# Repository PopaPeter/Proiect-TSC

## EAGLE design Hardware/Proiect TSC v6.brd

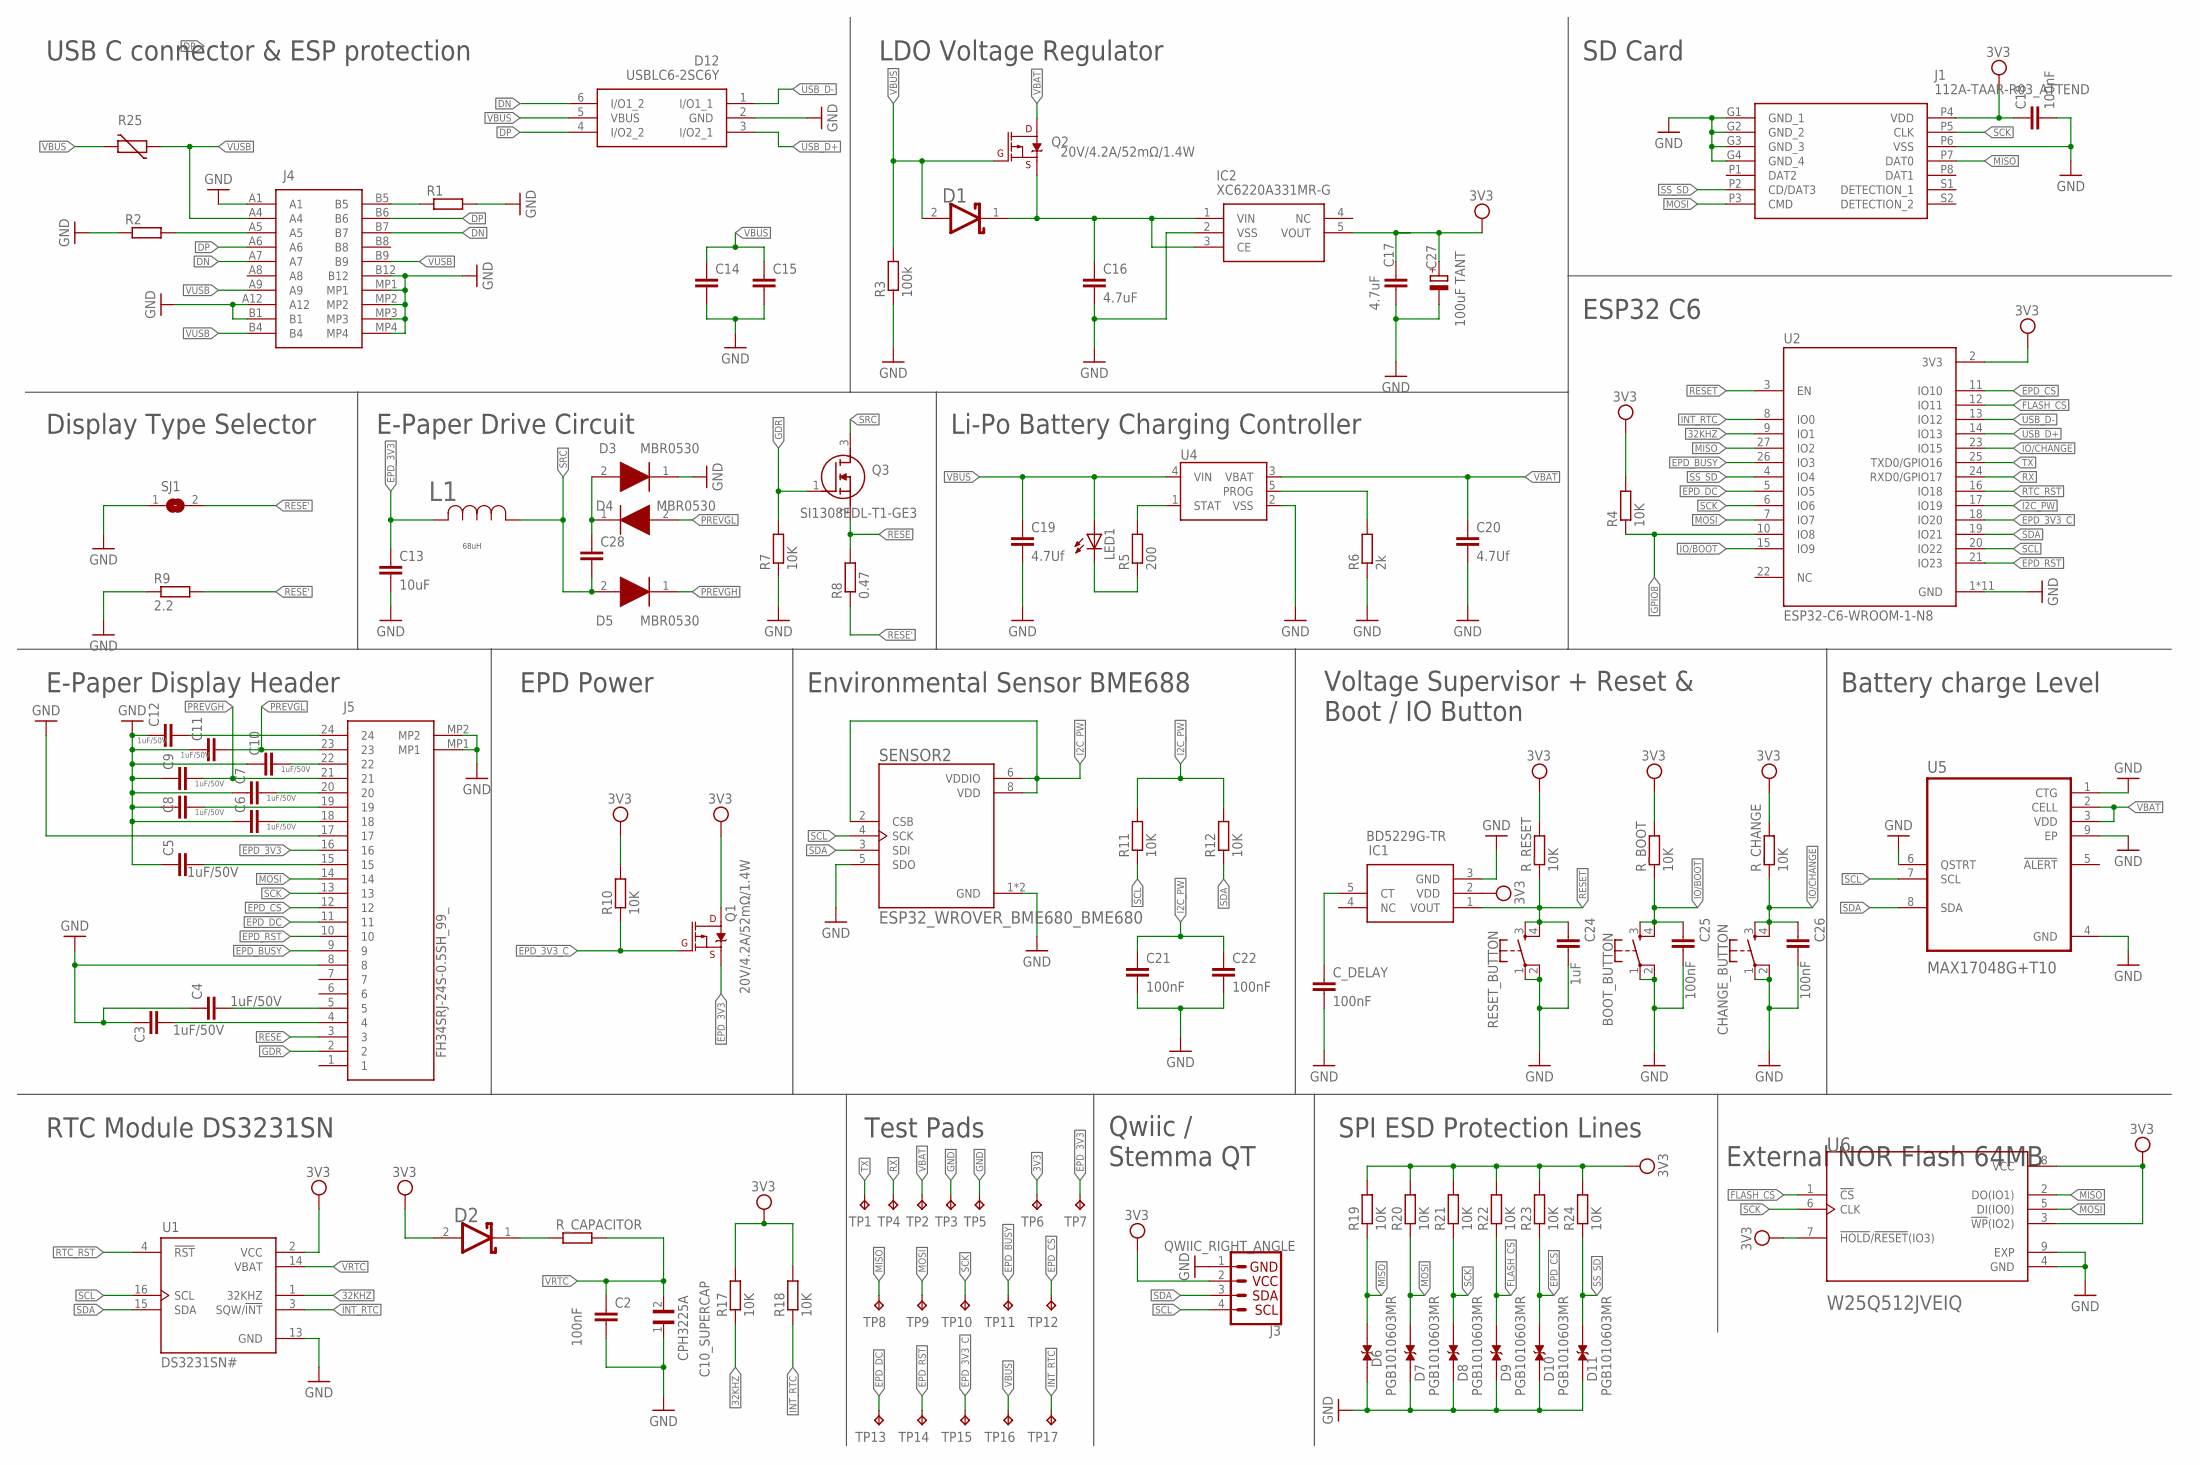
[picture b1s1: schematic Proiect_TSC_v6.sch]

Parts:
BOOT_BUTTON: BUTTON_CUSYOMV1; MYBUTTON
C2, C18, C21, C22, C25, C26: 100nF; ESP32_WROVER_EAGLE-LTSPICE_C0402
C3, C4, C5, C6, C7, C8, C9, C10, C11, C12: 1uF/50V; ESP32_WROVER_EAGLE-LTSPICE_C0402
C10_SUPERCAP: CPH3225A; CAPCP3225X100N
C13: 10uF; ESP32_WROVER_EAGLE-LTSPICE_C0402
C14, C15, C28: ESP32_WROVER_EAGLE-LTSPICE_CC0402; ESP32_WROVER_EAGLE-LTSPICE_C0402
C16, C17: 4.7uF; ESP32_WROVER_EAGLE-LTSPICE_C0402
C19, C20: 4.7Uf; ESP32_WROVER_EAGLE-LTSPICE_C0402
C24: 1uF; ESP32_WROVER_EAGLE-LTSPICE_C0402
C27: 100uF TANT; RCL_CT3528
CHANGE_BUTTON: BUTTON_CUSYOMV1; MYBUTTON
C_DELAY: 100nF; ESP32_WROVER_EAGLE-LTSPICE_C0402
D1, D2: ESP32_WROVER_AVX---SD0805S020S1R0_AVX_SD0805S020S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; ESP32_WROVER_AVX---SD0805S020S1R0_AVX_SD0805S020S1R0_0
D3, D4, D5: MBR0530; SOD3716X135N
D6, D7, D8, D9, D10, D11: PGB1010603MR; DIOC1608X36N
D12: USBLC6-2SC6Y; SOT95P280X145-6N
IC1: BD5229G-TR; SOT95P280X125-5N
IC2: XC6220A331MR-G; SOT95P280X120-5N
J1: 112A-TAAR-R03_ATTEND; 112ATAARR03ATTEND
J3: QWIIC_RIGHT_ANGLE; JST04_1MM_RA
J4: SAMACSYS_PARTS_USB4110-GF-A; SAMACSYS_PARTS_USB4110GFA
J5: FH34SRJ-24S-0.5SH_99_; FH34SRJ24S05SH99
L1: 744043680IND_4828-WE-TPC_WRE; IND_4828-WE-TPC_WRE
LED1: ADAFRUIT_LEDCHIP-LED0603; ADAFRUIT_CHIP-LED0603
Q1, Q2: 20V/4.2A/52mΩ/1.4W; ESP32_WROVER_SPARKFUN-DISCRETESEMI_SOT23-3
Q3: SI1308EDL-T1-GE3; SOT65P210X110-3N
R1, R2: ESP32_WROVER_EAGLE-LTSPICE_RR0402; ESP32_WROVER_EAGLE-LTSPICE_R0402
R3: 100k; ESP32_WROVER_EAGLE-LTSPICE_R0402
R4, R7, R10, R11, R12, R17, R18, R19, R20, R21, R22, R23, R24: 10K; ESP32_WROVER_EAGLE-LTSPICE_R0402
R5: 200; ESP32_WROVER_EAGLE-LTSPICE_R0402
R6: 2k; ESP32_WROVER_EAGLE-LTSPICE_R0402
R8: 0.47; ESP32_WROVER_EAGLE-LTSPICE_R0402
R9: 2.2; ESP32_WROVER_EAGLE-LTSPICE_R0402
R25: ESP32C6_VARISTORCN1812; ESP32C6_VARISTOR_CT/CN1812
RESET_BUTTON: BUTTON_CUSYOMV1; MYBUTTON
R_BOOT: 10K; ESP32_WROVER_EAGLE-LTSPICE_R0402
R_CAPACITOR: ESP32_WROVER_EAGLE-LTSPICE_RR0402; ESP32_WROVER_EAGLE-LTSPICE_R0402
R_CHANGE: 10K; ESP32_WROVER_EAGLE-LTSPICE_R0402
R_RESET: 10K; ESP32_WROVER_EAGLE-LTSPICE_R0402
SENSOR2: ESP32_WROVER_BME680_BME680; ESP32_WROVER_BME680_PSON80P300X300X100-8N
SJ1: SJ
TP1, TP2, TP3, TP4, TP5, TP6, TP7, TP8, TP9, TP10, TP11, TP12, TP13, TP14, TP15, TP16, TP17: TPTP20R; TP20R
U1: DS3231SN#; SOIC127P1032X265-16N
U2: ESP32-C6-WROOM-1-N8; XCVR_ESP32-C6-WROOM-1-N8
U4: ESP32_WROVER_SPARKFUN-IC-POWER_MCP73831; ESP32_WROVER_SPARKFUN-IC-POWER_SOT23-5
U5: MAX17048G+T10; SON50P200X200X80-9N
U6: W25Q512JVEIQ; SON127P600X800X80-9N

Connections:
3V3: C18.1, D2.2 (ANODE), IC1.2 (VDD), J1.P4 (VDD), J3.2, Q1.3 (D), R4.2, R10.2, R17.2, R18.2, R19.2, R20.2, R21.2, R22.2, R23.2, R24.2, R_BOOT.2, R_CHANGE.2, R_RESET.2, TP6.TP, U1.2 (VCC), U2.2 (3V3), U6.3 (!WP!(IO2)), U6.7 (!HOLD!/!RESET!(IO3)), U6.8 (VCC)
32KHZ: R17.1, U1.1 (32KHZ), U2.9 (IO1)
DN: D12.6 (I/O1_2), J4.A7, J4.B7
DP: D12.4 (I/O2_2), J4.A6, J4.B6
EPD_3V3: C13.1, J5.16, L1.2, Q1.2 (S), TP7.TP
EPD_3V3_C: Q1.1 (G), R10.1, TP15.TP, U2.18 (IO20)
EPD_BUSY: J5.9, TP11.TP, U2.26 (IO3)
EPD_CS: D10.2, J5.12, R23.1, TP12.TP, U2.11 (IO10)
EPD_DC: J5.11, TP13.TP, U2.5 (IO5)
EPD_RST: J5.10, TP14.TP, U2.21 (IO23)
FLASH_CS: D9.2, R22.1, U2.12 (IO11), U6.1 (!CS)
GDR: J5.2, Q3.1 (G), R7.2
GND: BOOT_BUTTON.1, BOOT_BUTTON.2, C2.2, C3.1, C4.1, C5.1, C6.1, C7.1, C8.1, C9.1, C10.1, C10_SUPERCAP.1, C11.1, C12.1, C13.2, C14.2, C15.2, C16.2, C17.2, C18.2, C19.2, C20.2, C21.2, C22.2, C24.2, C25.2, C26.2, C27.-, CHANGE_BUTTON.1, CHANGE_BUTTON.2, C_DELAY.2, D4.1 (K), D6.1, D7.1, D8.1, D9.1, D10.1, D11.1, D12.2 (GND), IC1.3 (GND), IC2.2 (VSS), J1.G1 (GND_1), J1.G2 (GND_2), J1.G3 (GND_3), J1.G4 (GND_4), J1.P6 (VSS), J3.1, J4.A1, J4.A12, J4.B1, J4.B12, J4.MP1, J4.MP2, J4.MP3, J4.MP4, J5.8, J5.17, J5.MP1, J5.MP2, R1.2, R2.1, R3.1, R6.1, R7.1, R9.1, RESET_BUTTON.1, RESET_BUTTON.2, SENSOR2.1 (GND), SENSOR2.5 (SDO), SENSOR2.7 (GND), SJ1.1, TP3.TP, TP5.TP, U1.13 (GND), U2.1 (GND), U2.28 (GND), U2.29_1 (GND), U2.29_2 (GND), U2.29_3 (GND), U2.29_4 (GND), U2.29_5 (GND), U2.29_6 (GND), U2.29_7 (GND), U2.29_8 (GND), U2.29_9 (GND), U4.2 (VSS), U5.1 (CTG), U5.4 (GND), U5.6 (QSTRT), U5.9 (EP), U6.4 (GND), U6.9 (EXP)
GPIO8: R4.1, U2.10 (IO8)
I2C_PW: C21.1, C22.1, R11.2, R12.2, SENSOR2.2 (CSB), SENSOR2.6 (VDDIO), SENSOR2.8 (VDD), U2.17 (IO19)
INT_RTC: R18.1, TP17.TP, U1.3 (SQW/!INT), U2.8 (IO0)
IO/BOOT: BOOT_BUTTON.3, BOOT_BUTTON.4, C25.1, R_BOOT.1, U2.15 (IO9)
IO/CHANGE: C26.1, CHANGE_BUTTON.3, CHANGE_BUTTON.4, R_CHANGE.1, U2.23 (IO15)
MISO: D6.2, J1.P7 (DAT0), R19.1, TP8.TP, U2.27 (IO2), U6.2 (DO(IO1))
MOSI: D7.2, J1.P3 (CMD), J5.14, R20.1, TP9.TP, U2.7 (IO7), U6.5 (DI(IO0))
unnamed: J4.A5, R2.2
unnamed: J4.B5, R1.1
unnamed: C16.1, D1.1 (CATHODE), IC2.1 (VIN), IC2.3 (CE), Q2.2 (S)
unnamed: C17.1, C27.+, IC2.5 (VOUT)
unnamed: R5.2, U4.1 (STAT)
unnamed: LED1.C, R5.1
unnamed: R6.2, U4.5 (PROG)
unnamed: C28.1, D3.1 (K), D4.2 (A)
unnamed: C12.2, J5.24
unnamed: C10.2, J5.22
unnamed: C7.2, J5.20
unnamed: C8.2, J5.19
unnamed: C6.2, J5.18
unnamed: C5.2, J5.15
unnamed: C4.2, J5.5
unnamed: C3.2, J5.4
unnamed: C_DELAY.1, IC1.5 (CT)
unnamed: U5.2 (CELL), U5.3 (VDD)
unnamed: D2.1 (CATHODE), R_CAPACITOR.1
PREVGH: C9.2, D5.1 (K), J5.21
PREVGL: C11.2, D3.2 (A), J5.23
RESE: J5.3, Q3.2 (S), R8.2
RESE': R8.1, R9.2, SJ1.2
RESET: C24.1, IC1.1 (VOUT), RESET_BUTTON.3, RESET_BUTTON.4, R_RESET.1, U2.3 (EN)
RTC_RST: U1.4 (!RST), U2.16 (IO18)
RX: TP4.TP, U2.24 (RXD0/GPIO17)
SCK: D8.2, J1.P5 (CLK), J5.13, R21.1, TP10.TP, U2.6 (IO6), U6.6 (CLK)
SCL: J3.4, R11.1, SENSOR2.4 (SCK), U1.16 (SCL), U2.20 (IO22)
SDA: J3.3, R12.1, SENSOR2.3 (SDI), U1.15 (SDA), U2.19 (IO21)
SRC: C28.2, D5.2 (A), L1.1, Q3.3 (D)
SS_SD: D11.2, J1.P2 (CD/DAT3), R24.1, U2.4 (IO4)
TX: TP1.TP, U2.25 (TXD0/GPIO16)
USB_D+: D12.3 (I/O2_1), U2.14 (IO13)
USB_D-: D12.1 (I/O1_1), U2.13 (IO12)
VBAT: C20.1, Q2.3 (D), TP2.TP, U4.3 (VBAT)
VBUS: C14.1, C15.1, C19.1, D1.2 (ANODE), D12.5 (VBUS), LED1.A, Q2.1 (G), R3.2, R25.2, TP16.TP, U4.4 (VIN)
VRTC: C2.1, C10_SUPERCAP.2, R_CAPACITOR.2, U1.14 (VBAT)
VUSB: J4.A4, J4.A9, J4.B4, J4.B9, R25.1

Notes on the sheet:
External NOR Flash 64MB
SPI ESD Protection Lines
Test Pads
Qwiic / Stemma QT
RTC Module DS3231SN
E-Paper Display Header
EPD Power
Environmental Sensor BME688
Voltage Supervisor + Reset & Boot / IO Button
Battery charge Level
ESP32 C6
Li-Po Battery Charging Controller
E-Paper Drive Circuit
Display Type Selector
USB C connector & ESP protection
LDO Voltage Regulator
SD Card
68uH

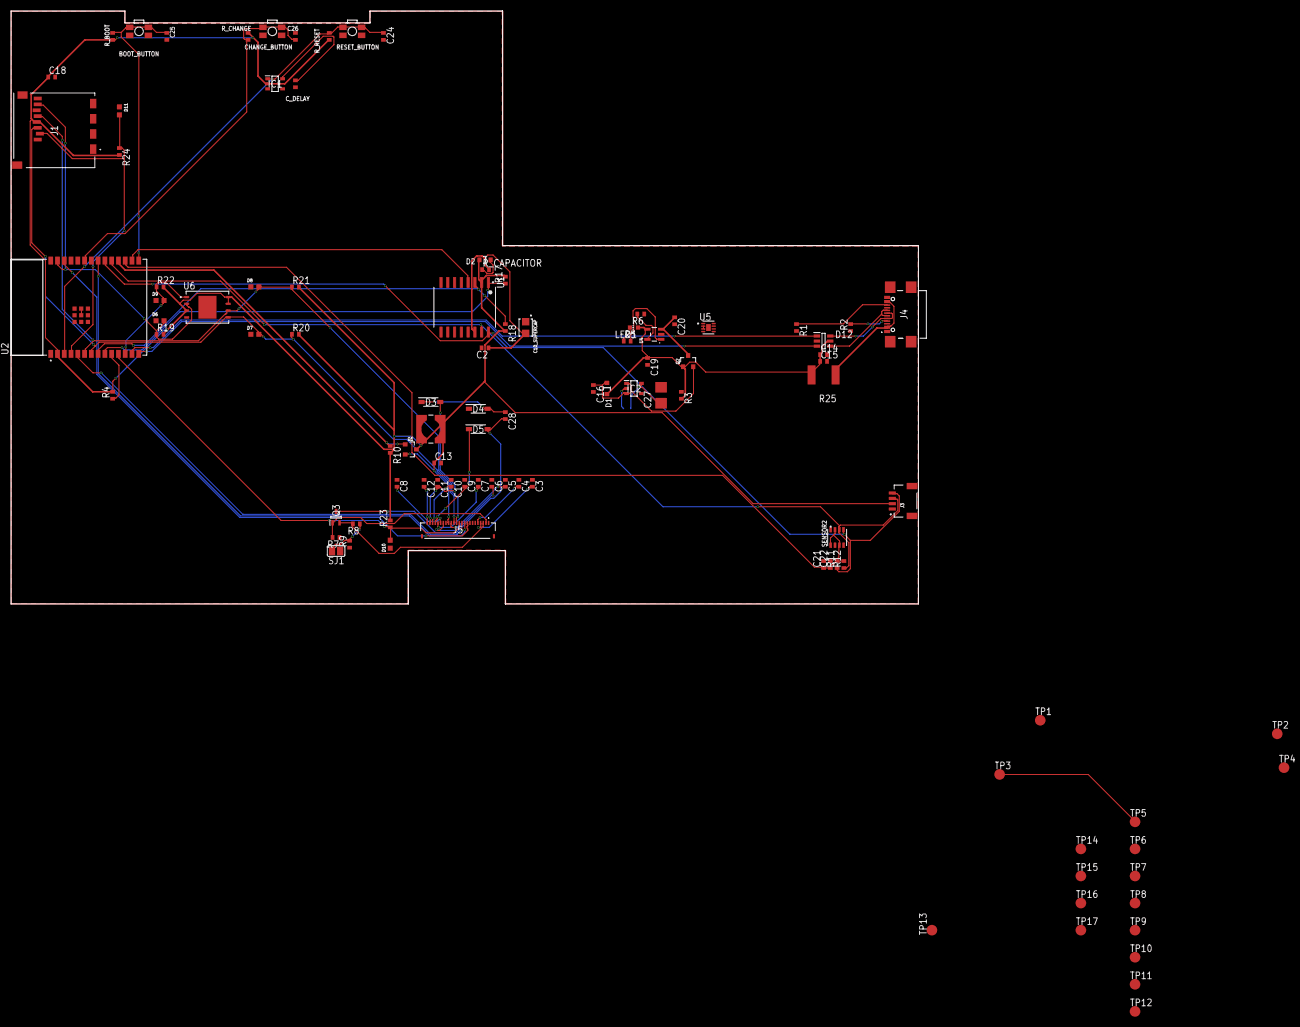
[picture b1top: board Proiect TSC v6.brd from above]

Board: 2 copper layers, 170.2 x 111.2 mm, 103 parts (1 on the bottom side), 58 nets.

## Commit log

2025-04-06 Rename Proiect TSC v6.brd to Hardware/Proiect TSC v6.brd
2025-04-06 Rename Proiect_TSC_v6.sch to Hardware/Proiect_TSC_v6.sch
2025-04-07 Create Manufacturing
2025-04-07 Create tsc

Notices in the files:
parts and their libraries:
COPYRIGHT: Copyright (C) 2024 Ultra Librarian. All rights reserved.
